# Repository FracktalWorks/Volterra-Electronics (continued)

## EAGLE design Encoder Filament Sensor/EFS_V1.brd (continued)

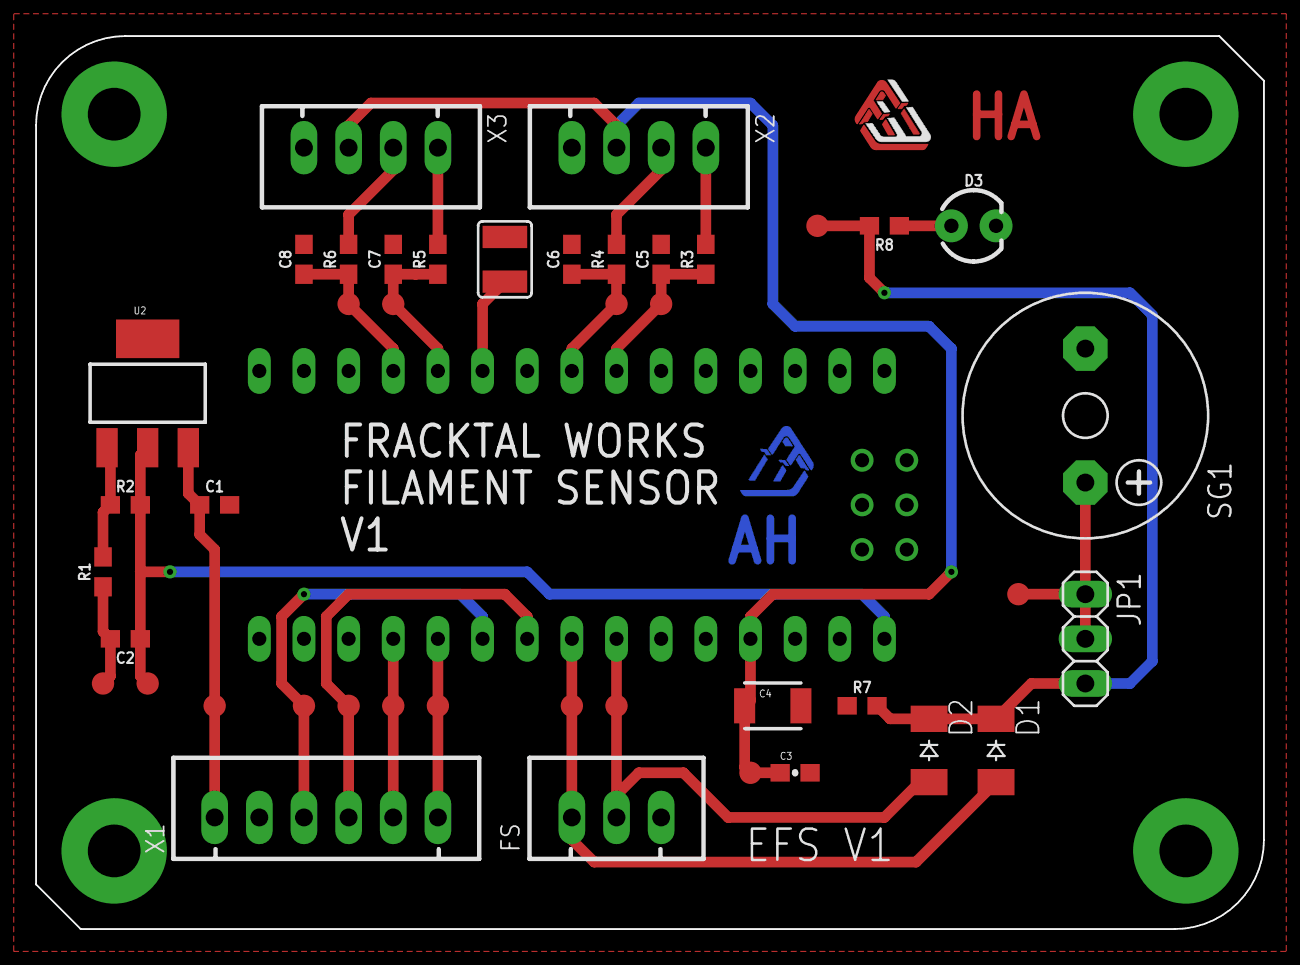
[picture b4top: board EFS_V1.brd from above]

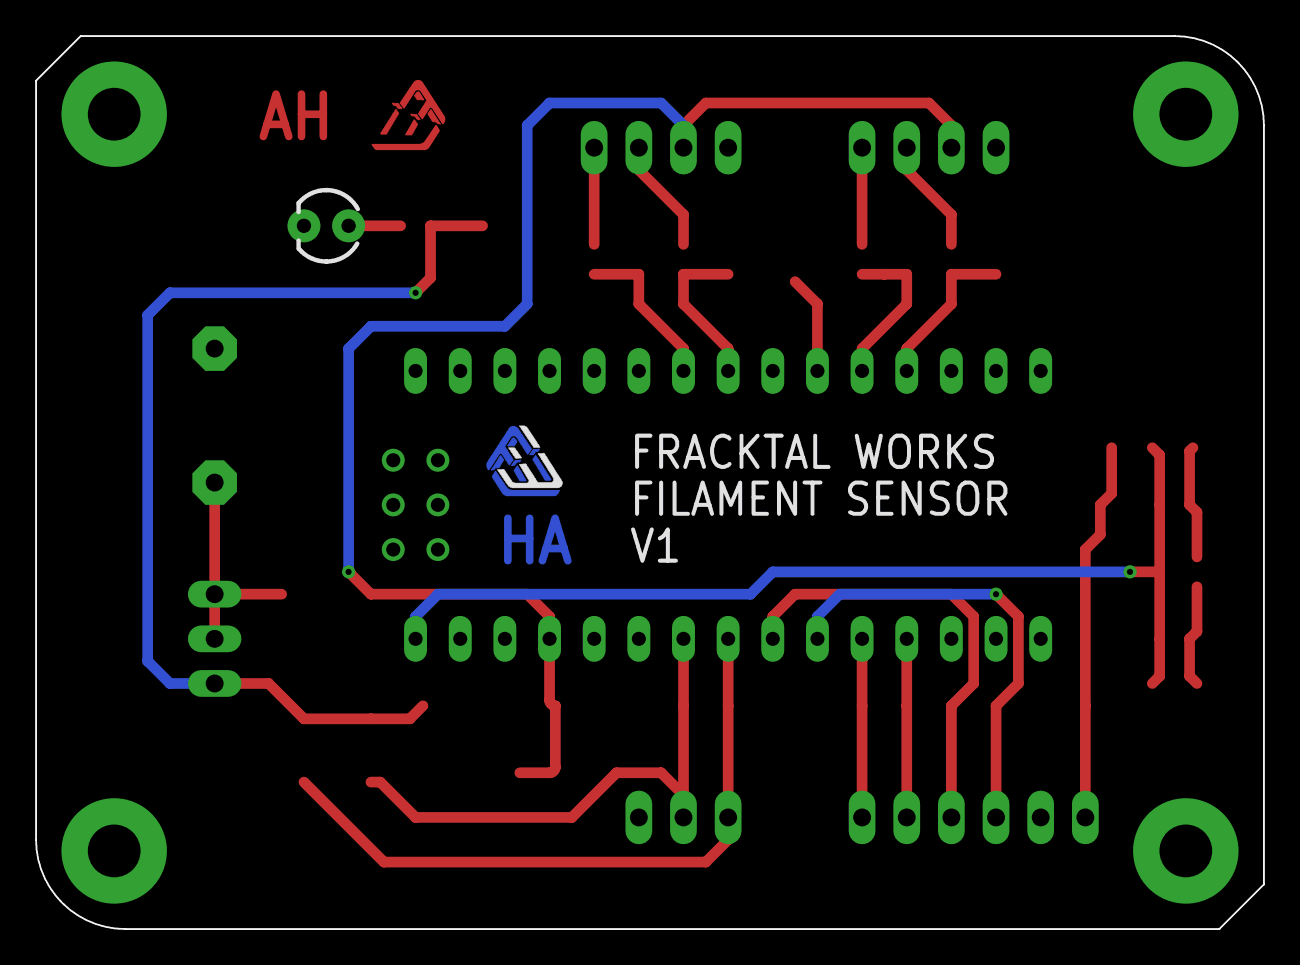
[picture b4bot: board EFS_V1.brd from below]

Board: 2 copper layers, 69.8 x 50.8 mm, 48 parts (2 on the bottom side), 23 nets.

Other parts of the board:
U$4: FWLOGO

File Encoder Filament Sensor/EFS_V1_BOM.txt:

Partlist

Exported from EFS_V1.brd at 27-04-2019 11:07

EAGLE Version 9.1.3 Copyright (c) 1988-2018 Autodesk, Inc.

Assembly variant: 

Part     Value              Package                    Library                                        Position (mil)        Orientation

C1       0.1uF              0603                       SparkFun-Capacitors                            (400 950)             R0
C2       1uf                0603                       SparkFun-Capacitors                            (200 650)             R180
C3       0.1uF              0603-CAP                   SparkFun-Capacitors                            (1700 350)            R0
C4       10uF               1210                       SparkFun-Capacitors                            (1650 500)            R0
C5       0.1uF              0603                       SparkFun-Capacitors                            (1400 1500)           R90
C6       0.1uF              0603                       SparkFun-Capacitors                            (1200 1500)           R90
C7       0.1uF              0603                       SparkFun-Capacitors                            (800 1500)            R90
C8       0.1uF              0603                       SparkFun-Capacitors                            (600 1500)            R90
D1       CGRM4007-G         SOD-123_MINI-SMA           diode                                          (2150 400)            R270
D2       CGRM4007-G         SOD-123_MINI-SMA           diode                                          (2000 400)            R270
D3       FAIL               LED_3MM                    SparkFun-LED                                   (2100 1575)           R0
FS       RPi Board (O)      JST-XH-03-PACKAGE-LONG-PAD Rembrandt                                      (1300 250)            R0
JP1                         1X03                       pinhead                                        (2350 650)            R270
R1        720R              0603                       SparkFun-Resistors                             (150 800)             R90
R2       100R               0603                       SparkFun-Resistors                             (200 950)             R0
R3       10k                0603                       SparkFun-Resistors                             (1500 1500)           R90
R4       10k                0603                       SparkFun-Resistors                             (1300 1500)           R90
R5       10k                0603                       SparkFun-Resistors                             (900 1500)            R90
R6       10k                0603                       SparkFun-Resistors                             (700 1500)            R90
R7       10k                0603                       SparkFun-Resistors                             (1850 500)            R0
R8       100R               0603                       SparkFun-Resistors                             (1900 1575)           R180
SG1      F/CM12P            F/CM12P                    buzzer                                         (2350 1150)           R270
SJ1                         SJW                        jumper                                         (1050 1500)           R90
TP1      TEST-POINT3X5      PAD.03X.05                 SparkFun-Connectors                            (400 500)             R90
TP2      TEST-POINT3X5      PAD.03X.05                 SparkFun-Connectors                            (250 550)             R90
TP3      TEST-POINT3X5      PAD.03X.05                 SparkFun-Connectors                            (1600 350)            R90
TP4      TEST-POINT3X5      PAD.03X.05                 SparkFun-Connectors                            (150 550)             R90
TP5      TEST-POINT3X5      PAD.03X.05                 SparkFun-Connectors                            (800 500)             R90
TP6      TEST-POINT3X5      PAD.03X.05                 SparkFun-Connectors                            (900 500)             R90
TP7      TEST-POINT3X5      PAD.03X.05                 SparkFun-Connectors                            (600 500)             R90
TP8      TEST-POINT3X5      PAD.03X.05                 SparkFun-Connectors                            (700 500)             R90
TP9      TEST-POINT3X5      PAD.03X.05                 SparkFun-Connectors                            (1400 1400)           R90
TP10     TEST-POINT3X5      PAD.03X.05                 SparkFun-Connectors                            (1300 1400)           R90
TP11     TEST-POINT3X5      PAD.03X.05                 SparkFun-Connectors                            (800 1400)            R90
TP12     TEST-POINT3X5      PAD.03X.05                 SparkFun-Connectors                            (700 1400)            R90
TP13     TEST-POINT3X5      PAD.03X.05                 SparkFun-Connectors                            (1200 500)            R90
TP14     TEST-POINT3X5      PAD.03X.05                 SparkFun-Connectors                            (1300 500)            R90
TP15     TEST-POINT3X5      PAD.03X.05                 SparkFun-Connectors                            (1750 1575)           R90
TP16     TEST-POINT3X5      PAD.03X.05                 SparkFun-Connectors                            (2200 750)            R90
U$1      NANO               NANO                       Arduino-clone                                  (1550 1050)           R90
U2       LM317              SOT223                     SparkFun-IC-Power                              (250 1200)            R0
X1       Carriage Board (I) JST-XH-06-PACKAGE-LONG-PAD Rembrandt Electronics - JST XH Connectors v1-0 (650 250)             R0
X2       ENC0               JST-XH-04-PACKAGE-LONG-PAD Rembrandt                                      (1350 1750)           R180
X3       ENC1               JST-XH-04-PACKAGE-LONG-PAD Rembrandt                                      (750 1750)            R180

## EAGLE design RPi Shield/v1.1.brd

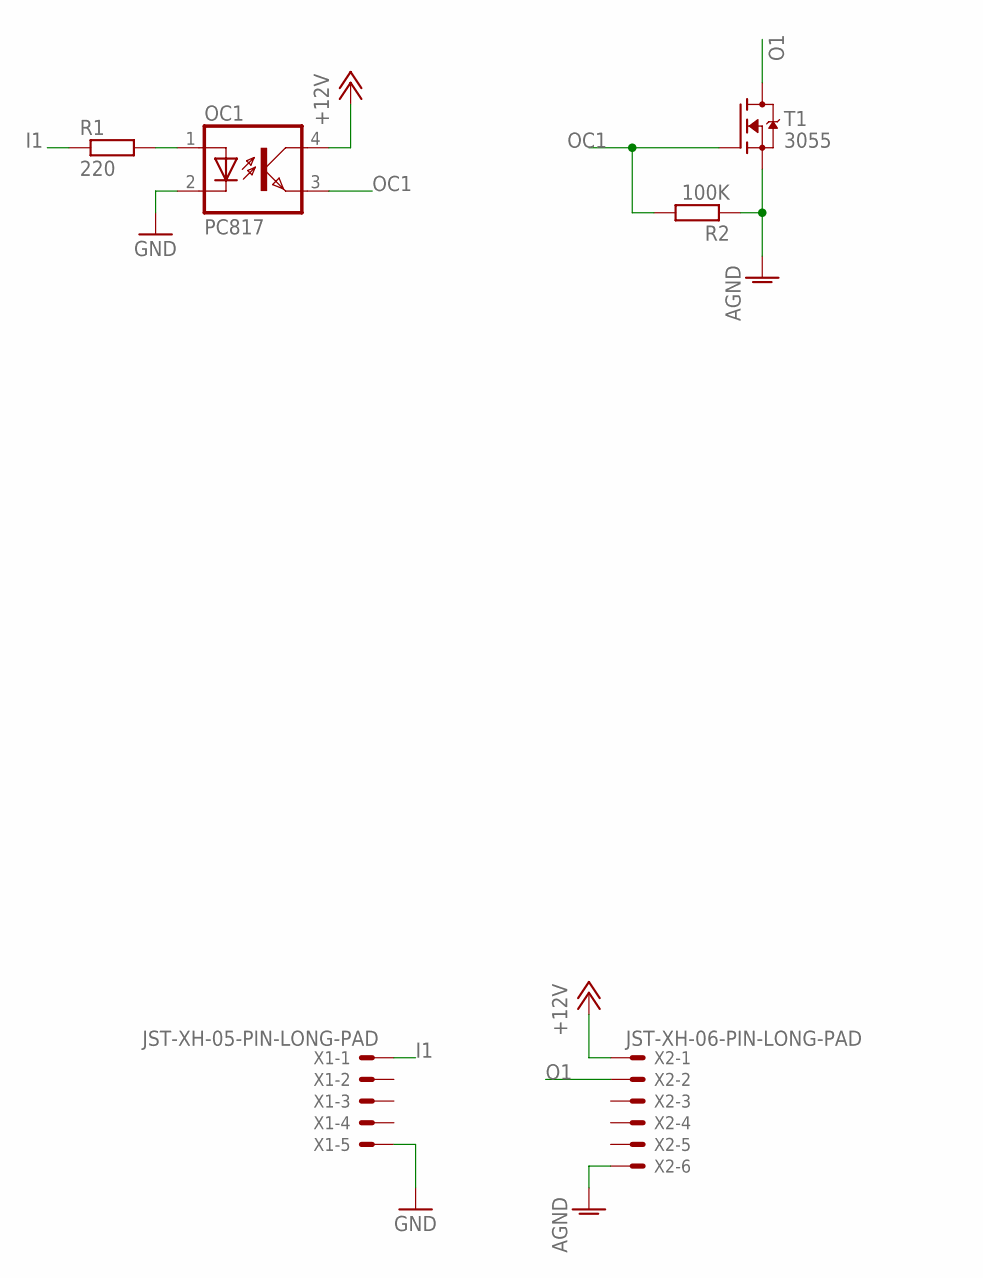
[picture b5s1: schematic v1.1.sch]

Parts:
OC1: PC817; DIL04
R1: 220; R0603
R2: 100K; R0603
T1: 3055; SOT223
X1: JST-XH-05-PIN-LONG-PAD; JST-XH-05-PACKAGE-LONG-PAD
X2: JST-XH-06-PIN-LONG-PAD; JST-XH-06-PACKAGE-LONG-PAD

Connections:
+12V: OC1.4 (COL), X2.1
AGND: R2.1, T1.3 (S), X2.6
GND: OC1.2 (C), X1.5
I1: R1.1, X1.1
unnamed: OC1.1 (A), R1.2
O1: T1.2 (D), T1.4 (D), X2.2
OC1: OC1.3 (EMIT), R2.2, T1.1 (G)

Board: 2 copper layers, 6 parts (0 on the bottom side), 7 nets, no tracks yet.

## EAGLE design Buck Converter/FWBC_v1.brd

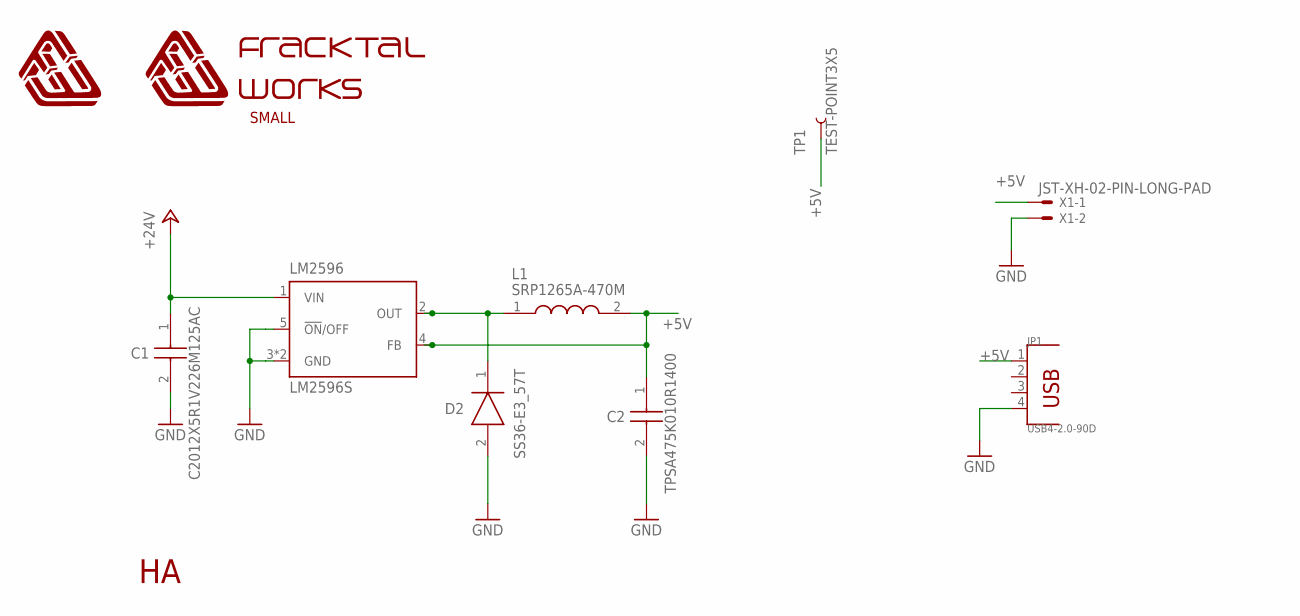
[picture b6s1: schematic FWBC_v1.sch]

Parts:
C1: C2012X5R1V226M125AC; CAPC2012X145N
C2: TPSA475K010R1400; CAPPM3216X180N
D2: SS36-E3_57T; DIOM7959X262N
JP1: USB4-2.0-90D; USB4+2P-2.0-90D
L1: SRP1265A-470M; SRP1265A
LM2596: LM2596S; LM2596_TO263-5
M_HA_1: HA_MARK
TP1: TEST-POINT3X5; PAD.03X.05
U$1: FWLOGO
U$2: FWLOGO_TEXT_SMALL
X1: JST-XH-02-PIN-LONG-PAD; JST-XH-02-PACKAGE-LONG-PAD

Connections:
+5V: C2.1, JP1.1, L1.2, LM2596.4 (FB), TP1.P$1, X1.1
+24V: C1.1, LM2596.1 (VIN)
GND: C1.2, C2.2, D2.2 (A), JP1.4, LM2596.3 (GND), LM2596.5 (!ON!/OFF), LM2596.6 (GND), X1.2
unnamed: D2.1 (K), L1.1, LM2596.2 (OUT)

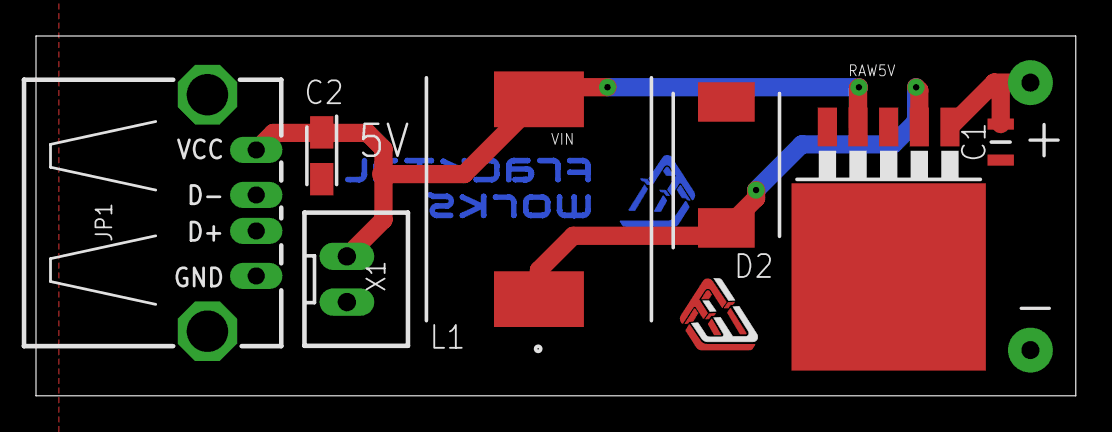
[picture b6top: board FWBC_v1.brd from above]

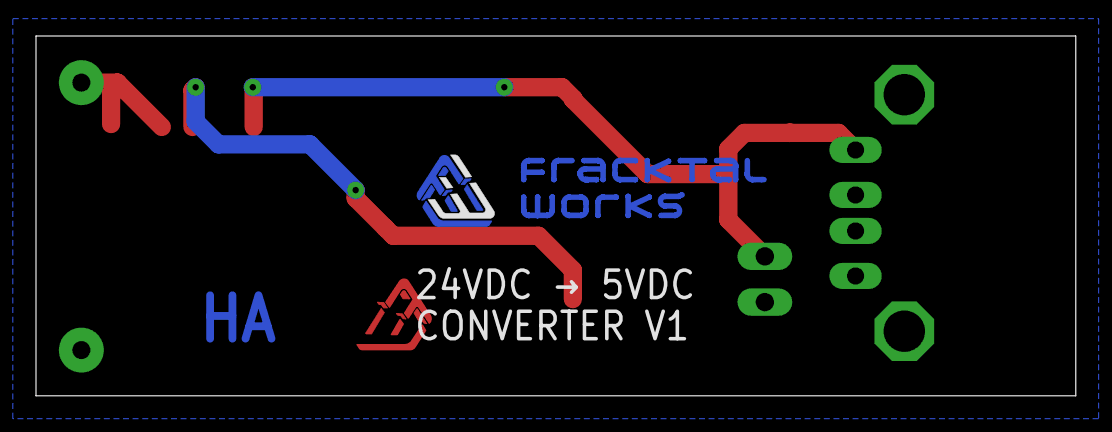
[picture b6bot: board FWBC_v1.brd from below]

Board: 2 copper layers, 57.8 x 20.0 mm, 11 parts (2 on the bottom side), 4 nets.

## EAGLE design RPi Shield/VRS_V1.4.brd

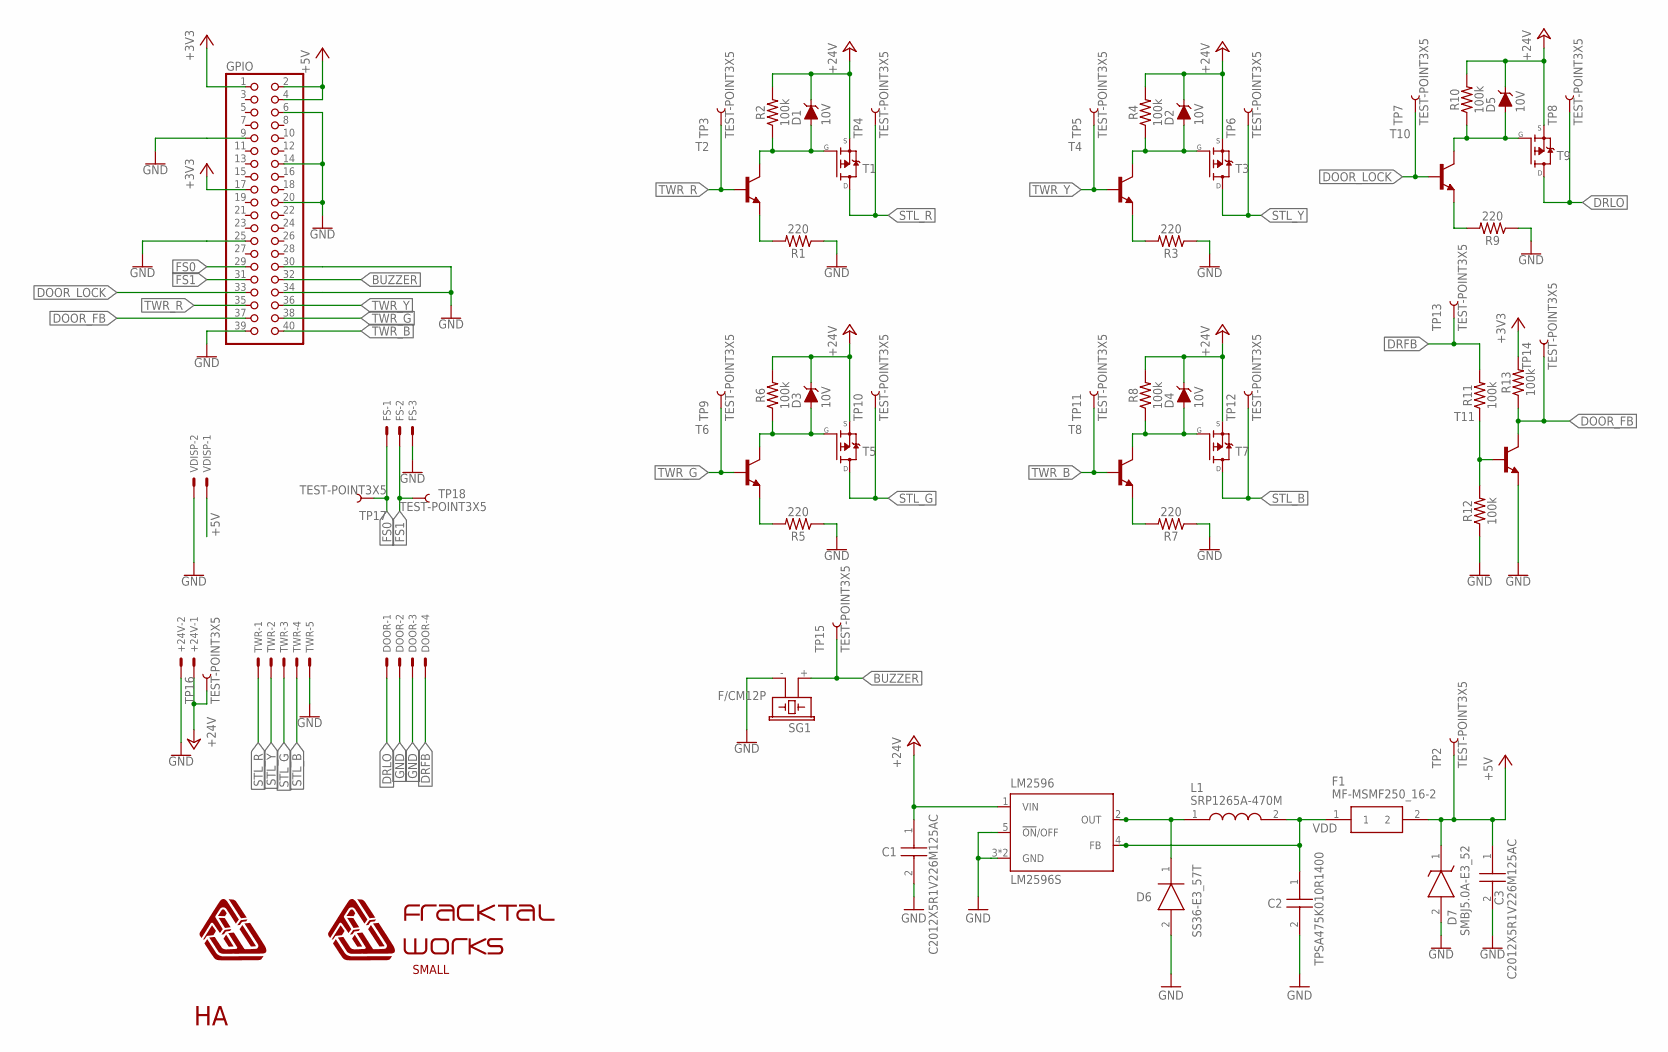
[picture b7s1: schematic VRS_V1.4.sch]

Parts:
+24V: JST-XH-02-PIN-LONG-PAD; JST-XH-02-PACKAGE-LONG-PAD
C1, C3: C2012X5R1V226M125AC; CAPC2012X145N
C2: TPSA475K010R1400; CAPPM3216X180N
D1, D2, D3, D4, D5: 10V; PANASONIC_SMINI2-F5-B
D6: SS36-E3_57T; DIOM7959X262N
D7: SMBJ5.0A-E3_52; DIOM5436X244N
DOOR: JST-XH-04-PIN-LONG-PAD; JST-XH-04-PACKAGE-LONG-PAD
F1: MF-MSMF250_16-2; FUSC4632X160N
FS: JST-XH-03-PIN-LONG-PAD; JST-XH-03-PACKAGE-LONG-PAD
GPIO: RASPBERRYPI_3B_GPIO
L1: SRP1265A-470M; SRP1265A
LM2596: LM2596S; LM2596_TO263-5
M_HA_1: HA_MARK
R1, R3, R5, R7, R9: 220; 0603
R2, R4, R6, R8, R10, R11, R12, R13: 100k; 0603
SG1: F/CM12P
T1, T3, T5, T7, T9: MOSFET_P_SOT223; MOSFET_SOT223
T2, T4, T6, T8, T10, T11: MMBT3904LT1-NPN-SOT23-BEC; SOT23-BEC
TP2, TP3, TP4, TP5, TP6, TP7, TP8, TP9, TP10, TP11, TP12, TP13, TP14, TP15, TP16, TP17, TP18: TEST-POINT3X5; PAD.03X.05
TWR: JST-XH-05-PIN-LONG-PAD; JST-XH-05-PACKAGE-LONG-PAD
U$1: FWLOGO_TEXT_SMALL
U$5: FWLOGO
VDISP: JST-XH-02-PIN-LONG-PAD; JST-XH-02-PACKAGE-LONG-PAD

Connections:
+3V3: GPIO.1, GPIO.17, R13.2
+5V: C3.1, D7.1 (K), F1.2, GPIO.2, GPIO.4, TP2.P$1, VDISP.1
+24V: +24V.1, C1.1, D1.C, D2.C, D3.C, D4.C, D5.C, LM2596.1 (VIN), R2.2, R4.2, R6.2, R8.2, R10.2, T1.3 (S), T3.3 (S), T5.3 (S), T7.3 (S), T9.3 (S), TP16.P$1
BUZZER: GPIO.32, SG1.+ (1), TP15.P$1
DOOR_FB: GPIO.37, R13.1, T11.C, TP14.P$1
DOOR_LOCK: GPIO.33, T10.B, TP7.P$1
DRFB: DOOR.4, R11.2, TP13.P$1
DRLO: DOOR.1, T9.2 (D), T9.4 (D), TP8.P$1
FS0: FS.1, GPIO.29, TP17.P$1
FS1: FS.2, GPIO.31, TP18.P$1
GND: +24V.2, C1.2, C2.2, C3.2, D6.2 (A), D7.2 (A), DOOR.2, DOOR.3, FS.3, GPIO.6, GPIO.9, GPIO.14, GPIO.20, GPIO.25, GPIO.30, GPIO.34, GPIO.39, LM2596.3 (GND), LM2596.5 (!ON!/OFF), LM2596.6 (GND), R1.1, R3.1, R5.1, R7.1, R9.1, R12.1, SG1.- (2), T11.E, TWR.5, VDISP.2
unnamed: R1.2, T2.E
unnamed: D6.1 (K), L1.1, LM2596.2 (OUT)
unnamed: D2.A, R4.1, T3.1 (G), T4.C
unnamed: D1.A, R2.1, T1.1 (G), T2.C
unnamed: R11.1, R12.2, T11.B
unnamed: R3.2, T4.E
unnamed: D3.A, R6.1, T5.1 (G), T6.C
unnamed: R5.2, T6.E
unnamed: D4.A, R8.1, T7.1 (G), T8.C
unnamed: R7.2, T8.E
unnamed: D5.A, R10.1, T9.1 (G), T10.C
unnamed: R9.2, T10.E
STL_B: T7.2 (D), T7.4 (D), TP12.P$1, TWR.4
STL_G: T5.2 (D), T5.4 (D), TP10.P$1, TWR.3
STL_R: T1.2 (D), T1.4 (D), TP4.P$1, TWR.1
STL_Y: T3.2 (D), T3.4 (D), TP6.P$1, TWR.2
TWR_B: GPIO.40, T8.B, TP11.P$1
TWR_G: GPIO.38, T6.B, TP9.P$1
TWR_R: GPIO.35, T2.B, TP3.P$1
TWR_Y: GPIO.36, T4.B, TP5.P$1
VDD: C2.1, F1.1, L1.2, LM2596.4 (FB)

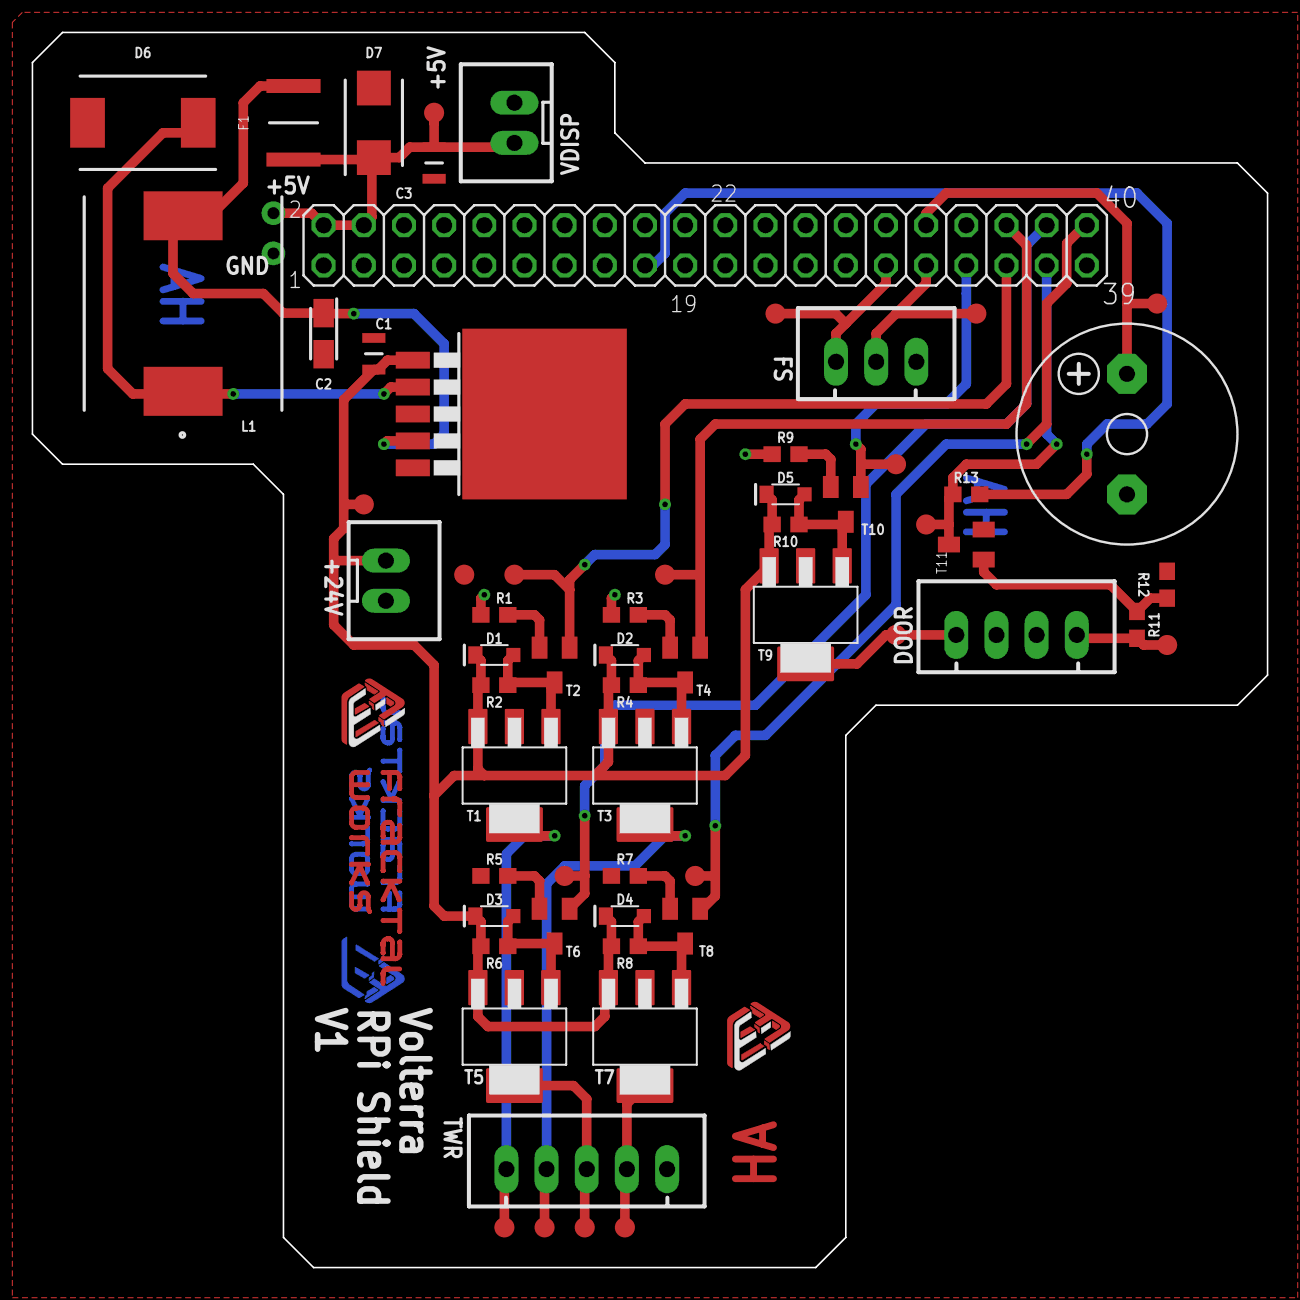
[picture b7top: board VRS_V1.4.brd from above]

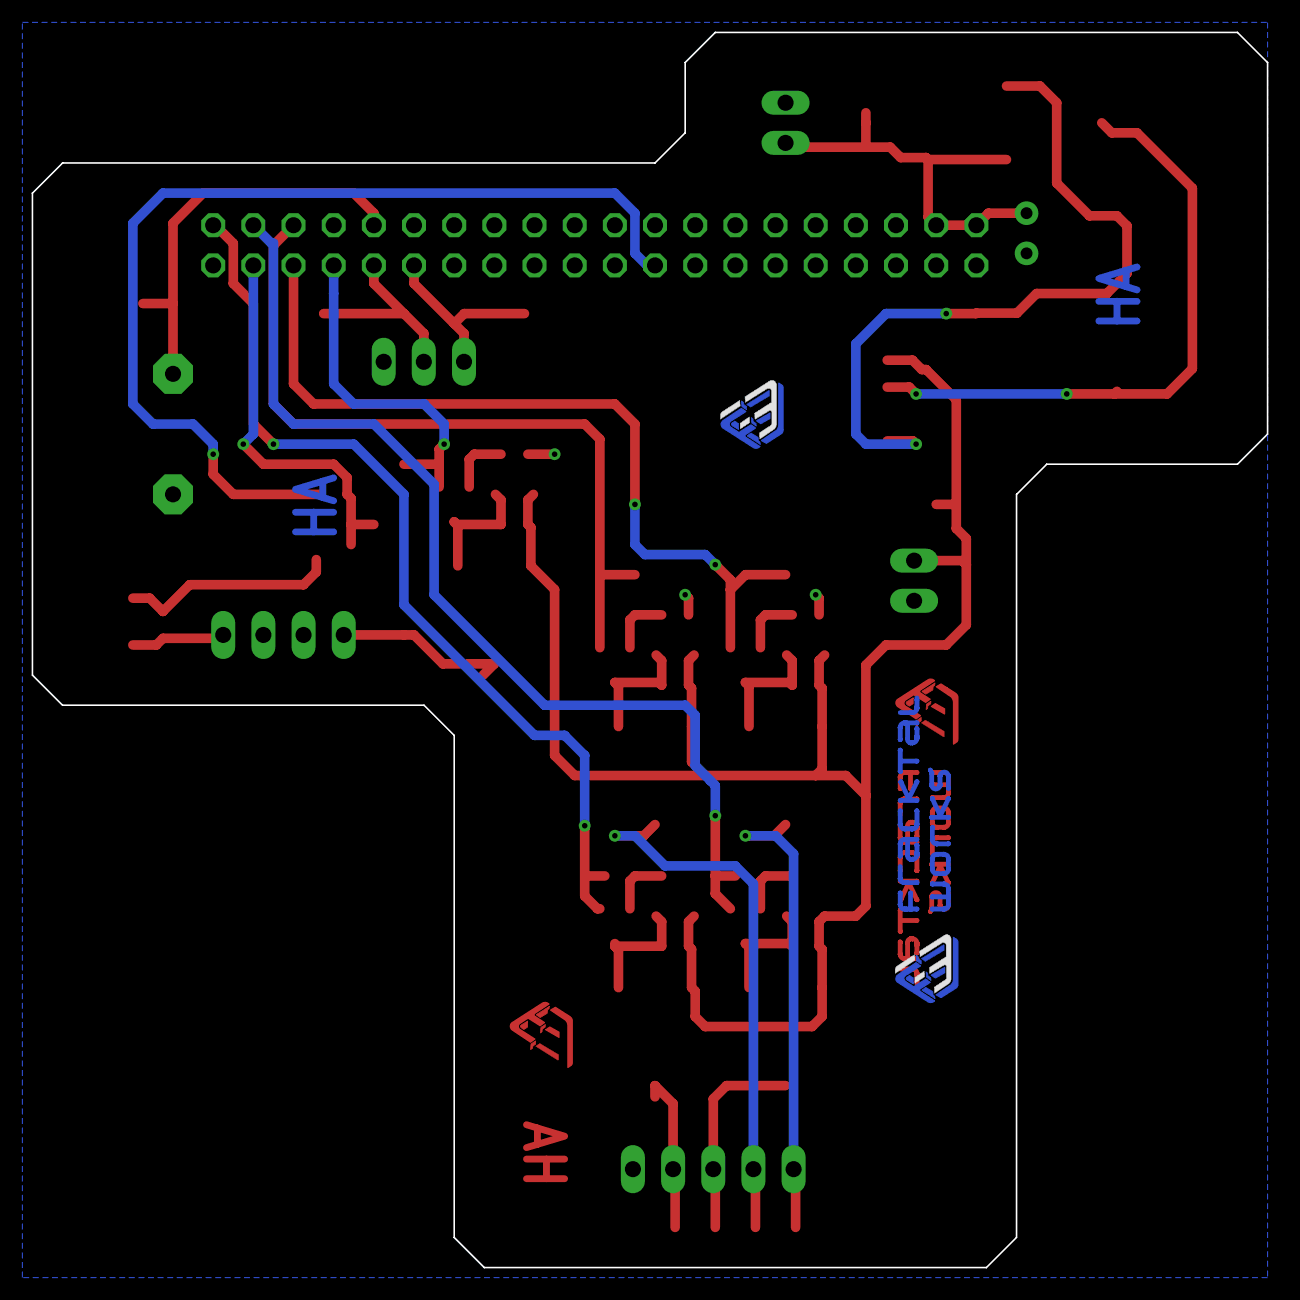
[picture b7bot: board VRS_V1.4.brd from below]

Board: 2 copper layers, 78.1 x 78.1 mm, 69 parts (4 on the bottom side), 32 nets.

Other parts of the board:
M_HA_2, M_HA_3: HA_MARK
TP1: TEST-POINT3X5; PAD.03X.05
U$2: FWLOGO_TEXT_SMALL
U$3: FWLOGO

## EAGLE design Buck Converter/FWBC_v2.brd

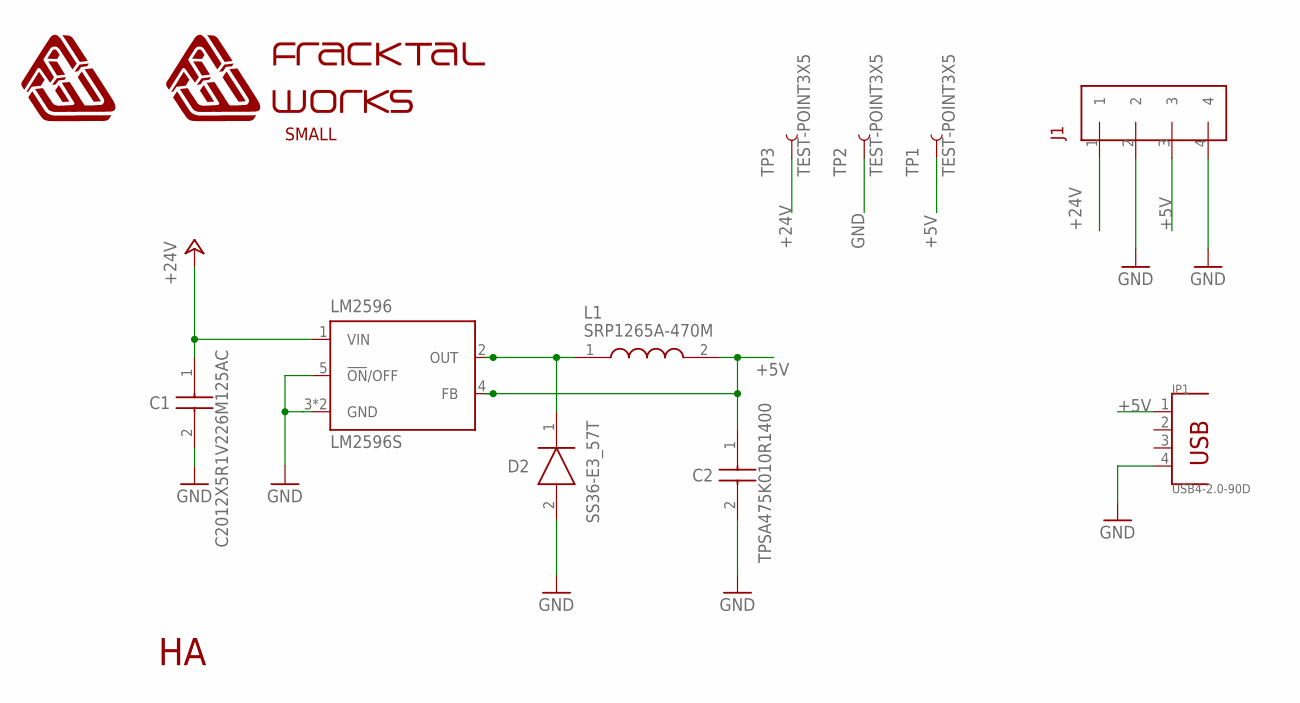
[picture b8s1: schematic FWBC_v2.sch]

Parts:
C1: C2012X5R1V226M125AC; CAPC2012X145N
C2: TPSA475K010R1400; CAPPM3216X180N
D2: SS36-E3_57T; DIOM7959X262N
J1: TERMINALBLOCK/TOYO/4PIN/5MMPITCH
JP1: USB4-2.0-90D; USB4+2P-2.0-90D
L1: SRP1265A-470M; SRP1265A
LM2596: LM2596S; LM2596_TO263-5
M_HA_1: HA_MARK
TP1, TP2, TP3: TEST-POINT3X5; PAD.03X.05
U$1: FWLOGO
U$2: FWLOGO_TEXT_SMALL

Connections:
+5V: C2.1, J1.3, JP1.1, L1.2, LM2596.4 (FB), TP1.P$1
+24V: C1.1, J1.1, LM2596.1 (VIN), TP3.P$1
GND: C1.2, C2.2, D2.2 (A), J1.2, J1.4, JP1.4, LM2596.3 (GND), LM2596.5 (!ON!/OFF), LM2596.6 (GND), TP2.P$1
unnamed: D2.1 (K), L1.1, LM2596.2 (OUT)

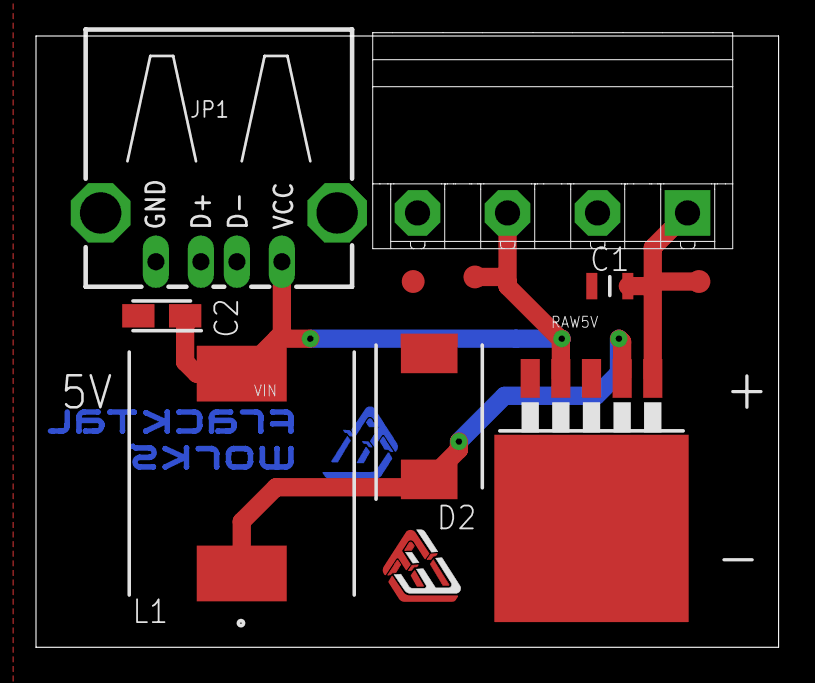
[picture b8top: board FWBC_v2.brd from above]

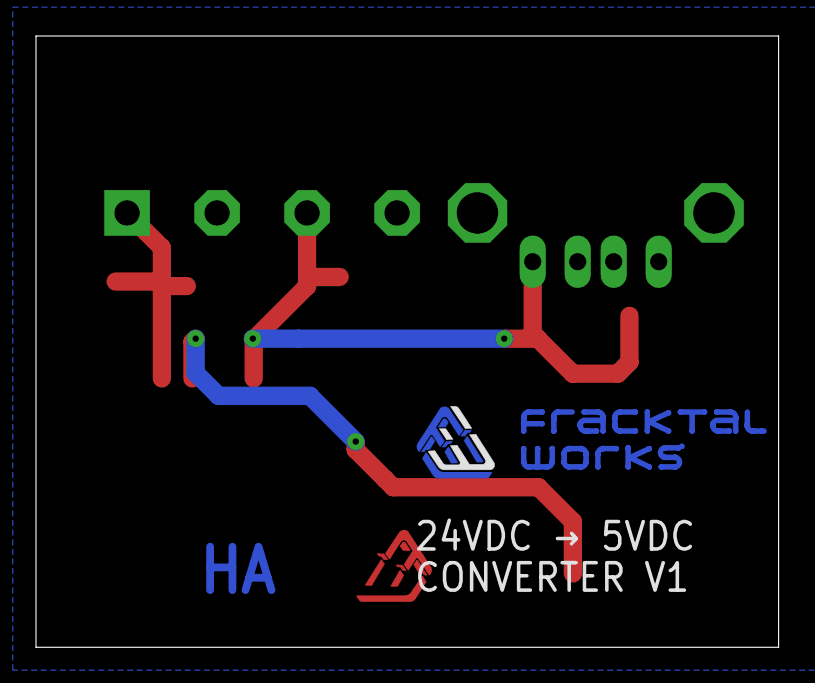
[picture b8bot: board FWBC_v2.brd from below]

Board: 2 copper layers, 41.3 x 34.0 mm, 13 parts (2 on the bottom side), 4 nets.

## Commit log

2020-01-10 added .gitignore
2020-01-10 cleaned up folders
2020-01-10 modded gitignore
2020-01-16 added partlist
2020-01-17 made chnages to volterra rpi board and exported gerber for manufacturing
2020-01-17 added cam file
2020-08-12 added MKS gen daughter board files
2020-08-12 removed old files
2021-12-28 BORADS FOR MKS GEN L 2.1
2021-12-28 MKS GEN L 2.1
    CHANGES MADE
